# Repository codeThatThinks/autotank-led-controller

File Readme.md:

# autotank-led-hw

A CANbus-enabled LED and GPIO controller -- PCB design files

## Theory of Operation

The controller listens for messages on the CANbus and drives two addressable RGB LED strips and four general-purpose open-collector outputs. It also monitors four general-purpose inputs and can send CANbus messages or change outputs in response to events.

The outputs are rated for 1A each and are intended to drive LED lights, such as headlights, tail lights, etc. The inputs are active-high and intended for body sensors and switches, such as a door switch.

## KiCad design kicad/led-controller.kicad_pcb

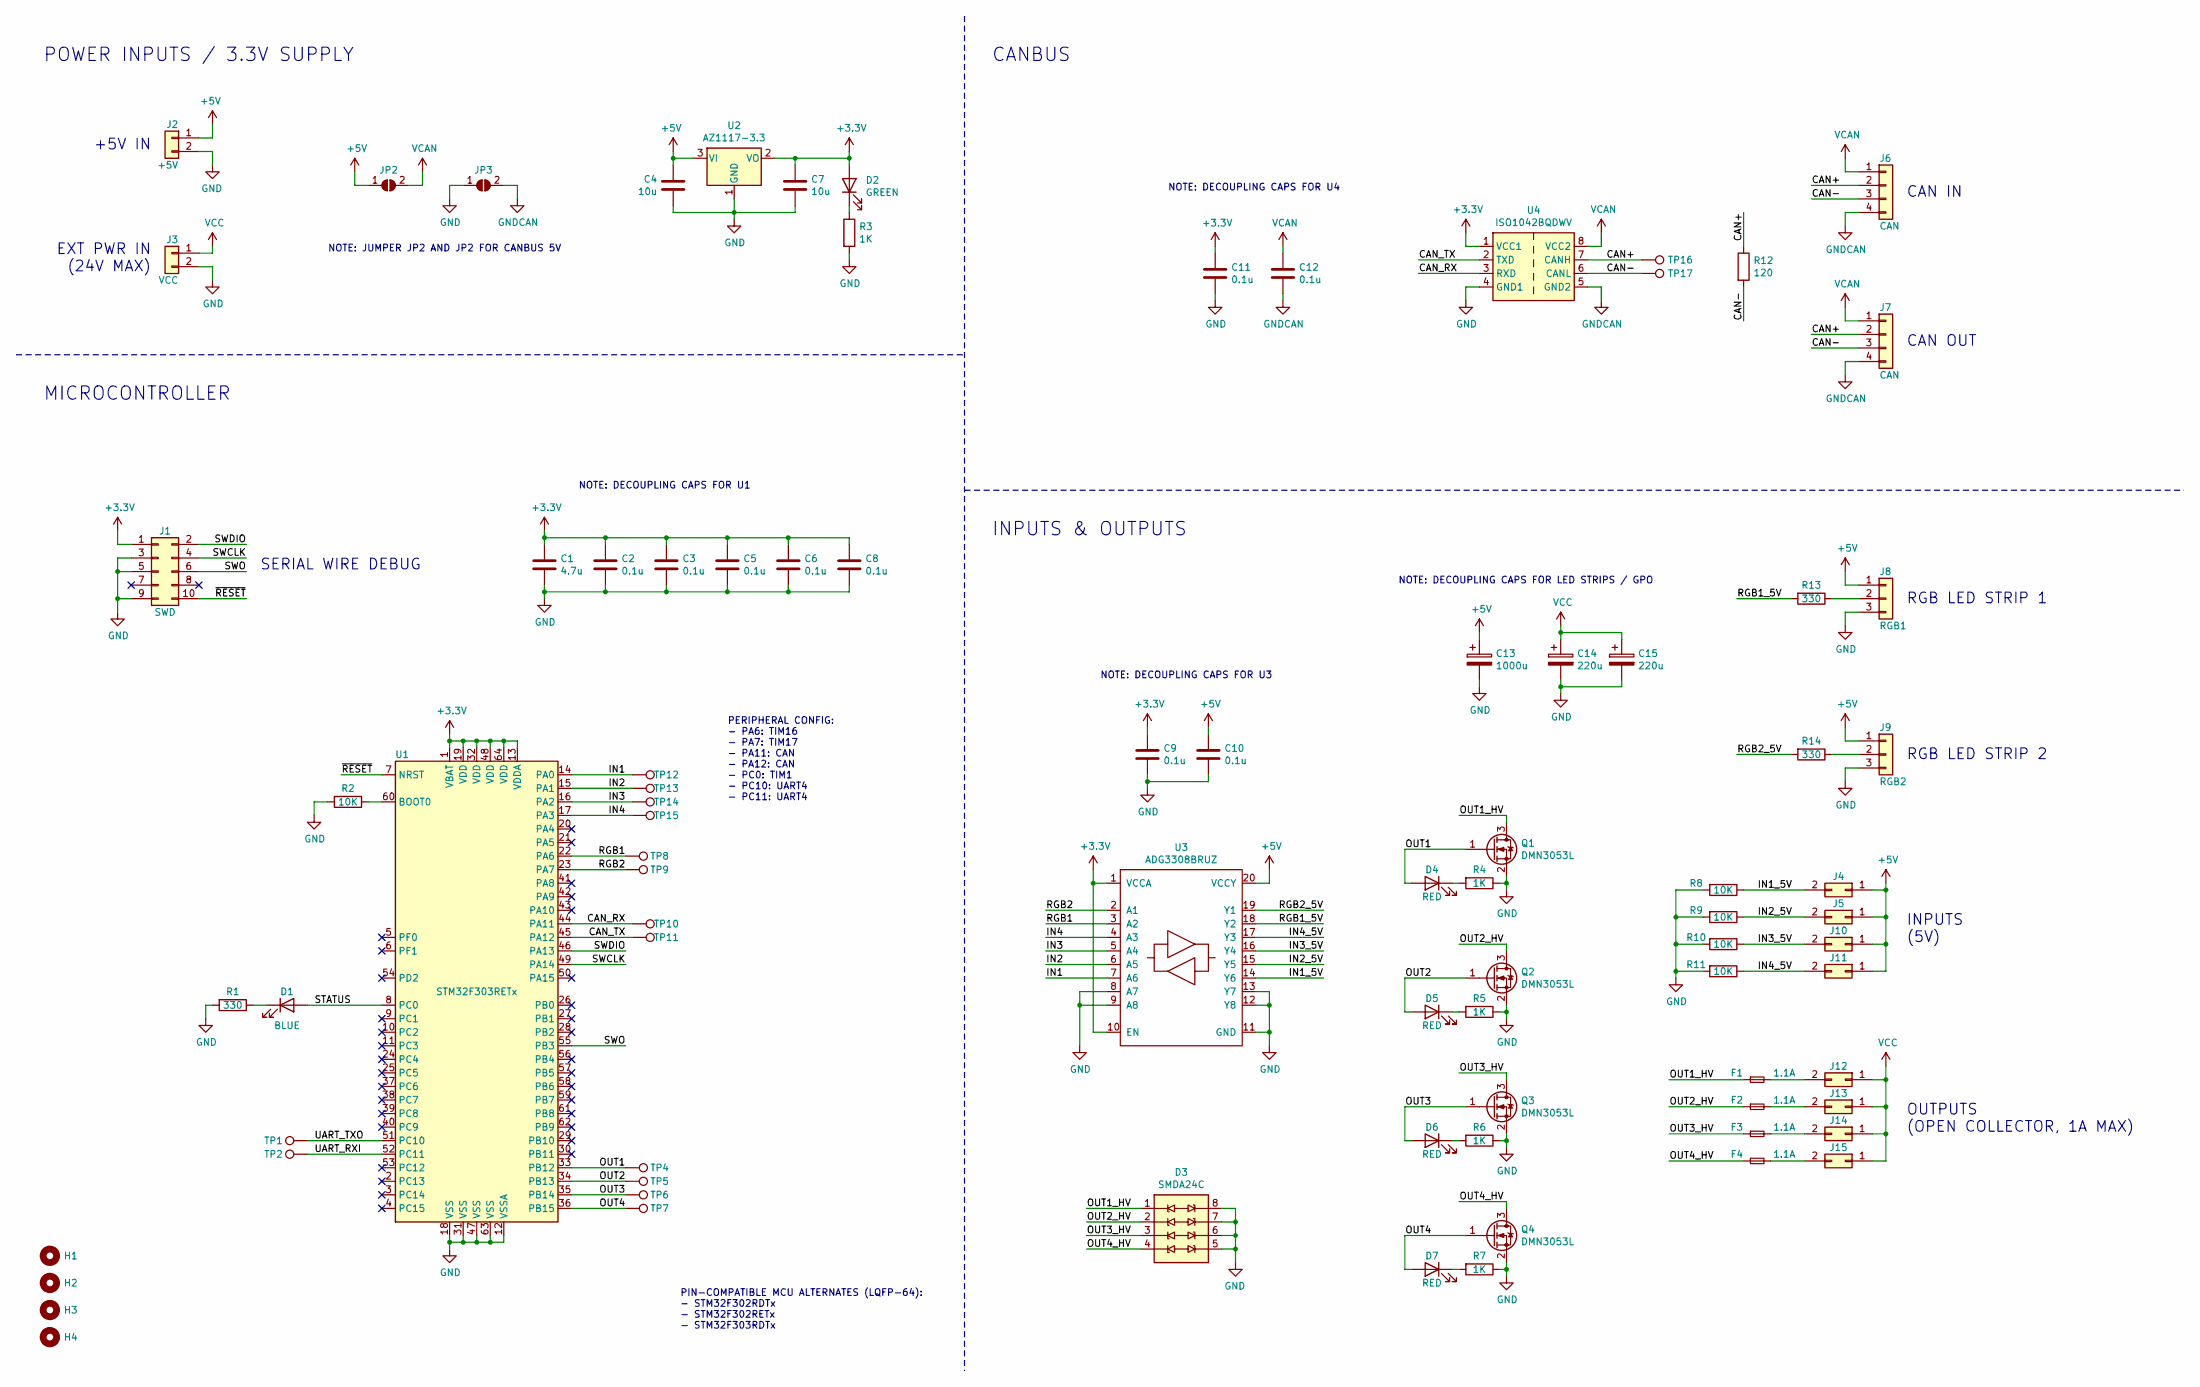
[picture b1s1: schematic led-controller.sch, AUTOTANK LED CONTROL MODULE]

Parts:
C1: 4.7u; C_0805_2012Metric
C2, C3, C5, C6, C8, C9, C10, C11, C12: 0.1u; C_0603_1608Metric
C4, C7: 10u; C_0805_2012Metric
C13: 1000u; CP_Radial_D8.0mm_P3.50mm
C14, C15: 220u; CP_Radial_D8.0mm_P3.50mm
D1: BLUE; LED_0603_1608Metric
D2: GREEN; LED_0603_1608Metric
D3: SMDA24C; SO-8_5.3x6.2mm_P1.27mm
D4, D5, D6, D7: RED; LED_0603_1608Metric
F1, F2, F3, F4: 1.1A; Fuse_1812_4532Metric_Castellated
H1, H2, H3, H4: MountingHole; MountingHole_3.2mm_M3
J1: SWD; PinHeader_2x05_P2.54mm_Vertical
J2: +5V; JST_XH_B2B-XH-AM_1x02_P2.50mm_Vertical
J3: VCC; JST_XH_B2B-XH-AM_1x02_P2.50mm_Vertical
J4: IN1; JST_XH_B2B-XH-AM_1x02_P2.50mm_Vertical
J5: IN2; JST_XH_B2B-XH-AM_1x02_P2.50mm_Vertical
J6, J7: CAN; JST_XH_B4B-XH-AM_1x04_P2.50mm_Vertical
J8: RGB1; JST_XH_B3B-XH-AM_1x03_P2.50mm_Vertical
J9: RGB2; JST_XH_B3B-XH-AM_1x03_P2.50mm_Vertical
J10: IN3; JST_XH_B2B-XH-AM_1x02_P2.50mm_Vertical
J11: IN4; JST_XH_B2B-XH-AM_1x02_P2.50mm_Vertical
J12: OUT1; JST_XH_B2B-XH-AM_1x02_P2.50mm_Vertical
J13: OUT2; JST_XH_B2B-XH-AM_1x02_P2.50mm_Vertical
J14: OUT3; JST_XH_B2B-XH-AM_1x02_P2.50mm_Vertical
J15: OUT4; JST_XH_B2B-XH-AM_1x02_P2.50mm_Vertical
JP2, JP3: SolderJumper_2_Open; SolderJumper-2_P1.3mm_Open_RoundedPad1.0x1.5mm
Q1, Q2, Q3, Q4: DMN3053L; SOT-23
R1, R13, R14: 330; R_0603_1608Metric
R2, R8, R9, R10, R11: 10K; R_0603_1608Metric
R3, R4, R5, R6, R7: 1K; R_0603_1608Metric
R12: 120; R_0603_1608Metric
TP1: TXO; TestPoint_THTPad_D1.0mm_Drill0.5mm
TP2: RXI; TestPoint_THTPad_D1.0mm_Drill0.5mm
TP4: OUT1; TestPoint_THTPad_D1.0mm_Drill0.5mm
TP5: OUT2; TestPoint_THTPad_D1.0mm_Drill0.5mm
TP6: OUT3; TestPoint_THTPad_D1.0mm_Drill0.5mm
TP7: OUT4; TestPoint_THTPad_D1.0mm_Drill0.5mm
TP8: RGB1; TestPoint_THTPad_D1.0mm_Drill0.5mm
TP9: RGB2; TestPoint_THTPad_D1.0mm_Drill0.5mm
TP10: RX; TestPoint_THTPad_D1.0mm_Drill0.5mm
TP11: TX; TestPoint_THTPad_D1.0mm_Drill0.5mm
TP12: IN1; TestPoint_THTPad_D1.0mm_Drill0.5mm
TP13: IN2; TestPoint_THTPad_D1.0mm_Drill0.5mm
TP14: IN3; TestPoint_THTPad_D1.0mm_Drill0.5mm
TP15: IN4; TestPoint_THTPad_D1.0mm_Drill0.5mm
TP16: H; TestPoint_THTPad_D1.0mm_Drill0.5mm
TP17: L; TestPoint_THTPad_D1.0mm_Drill0.5mm
U1: STM32F303RETx; LQFP-64_10x10mm_P0.5mm
U2: AZ1117-3.3; SOT-223-3_TabPin2
U3: ADG3308BRUZ; TSSOP-20_4.4x6.5mm_P0.65mm
U4: ISO1042BQDWV; SOIC-8_7.5x5.85mm_P1.27mm

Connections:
+3V3: C1.1, C2.1, C3.1, C5.1, C6.1, C7.1, C8.1, C9.1, C11.1, D2.2 (A), J1.1, U1.1 (VBAT), U1.13 (VDDA), U1.19 (VDD), U1.32 (VDD), U1.48 (VDD), U1.64 (VDD), U2.2 (VO), U3.1 (VCCA), U3.10 (EN), U4.1 (VCC1)
+5V: C4.2, C10.1, C13.1, J2.1, J4.1, J5.1, J8.1, J9.1, J10.1, J11.1, JP2.1 (A), U2.3 (VI), U3.20 (VCCY)
/CAN+: J6.2, J7.2, R12.1, TP16.1, U4.7 (CANH)
/CAN-: J6.3, J7.3, R12.2, TP17.1, U4.6 (CANL)
/CAN_RX: TP10.1, U1.44 (PA11), U4.3 (RXD)
/CAN_TX: TP11.1, U1.45 (PA12), U4.2 (TXD)
/IN1: TP12.1, U1.14 (PA0), U3.7 (A6)
/IN1_5V: J4.2, R8.1, U3.14 (Y6)
/IN2: TP13.1, U1.15 (PA1), U3.6 (A5)
/IN2_5V: J5.2, R9.1, U3.15 (Y5)
/IN3: TP14.1, U1.16 (PA2), U3.5 (A4)
/IN3_5V: J10.2, R10.1, U3.16 (Y4)
/IN4: TP15.1, U1.17 (PA3), U3.4 (A3)
/IN4_5V: J11.2, R11.1, U3.17 (Y3)
/OUT1: D4.2 (A), Q1.1 (G), TP4.1, U1.33 (PB12)
/OUT1_HV: D3.1 (TVS1A), F1.1, Q1.3 (D)
/OUT2: D5.2 (A), Q2.1 (G), TP5.1, U1.34 (PB13)
/OUT2_HV: D3.2 (TVS2A), F2.1, Q2.3 (D)
/OUT3: D6.2 (A), Q3.1 (G), TP6.1, U1.35 (PB14)
/OUT3_HV: D3.3 (TVS3A), F3.1, Q3.3 (D)
/OUT4: D7.2 (A), Q4.1 (G), TP7.1, U1.36 (PB15)
/OUT4_HV: D3.4 (TVS4A), F4.1, Q4.3 (D)
/RGB1: TP8.1, U1.22 (PA6), U3.3 (A2)
/RGB1_5V: R13.2, U3.18 (Y2)
/RGB2: TP9.1, U1.23 (PA7), U3.2 (A1)
/RGB2_5V: R14.2, U3.19 (Y1)
/STATUS: D1.2 (A), U1.8 (PC0)
/SWCLK: J1.4, U1.49 (PA14)
/SWDIO: J1.2, U1.46 (PA13)
/SWO: J1.6, U1.55 (PB3)
/UART_RXI: TP2.1, U1.52 (PC11)
/UART_TXO: TP1.1, U1.51 (PC10)
/~RESET: J1.10, U1.7 (NRST)
GND: C1.2, C2.2, C3.2, C4.1, C5.2, C6.2, C7.2, C8.2, C9.2, C10.2, C11.2, C13.2, C14.2, C15.2, D3.5 (TVS4B), D3.6 (TVS3B), D3.7 (TVS2B), D3.8 (TVS1A), J1.3, J1.5, J1.9, J2.2, J3.2, J8.3, J9.3, JP3.1 (A), Q1.2 (S), Q2.2 (S), Q3.2 (S), Q4.2 (S), R1.2, R2.2, R3.2, R4.1, R5.1, R6.1, R7.1, R8.2, R9.2, R10.2, R11.2, U1.12 (VSSA), U1.18 (VSS), U1.31 (VSS), U1.47 (VSS), U1.63 (VSS), U2.1 (GND), U3.8 (A7), U3.9 (A8), U3.11 (GND), U3.12 (Y8), U3.13 (Y7), U4.4 (GND1)
GNDCAN: C12.2, J6.4, J7.4, JP3.2 (B), U4.5 (GND2)
unnamed: D1.1 (K), R1.1
unnamed: D2.1 (K), R3.1
unnamed: D4.1 (K), R4.2
unnamed: D5.1 (K), R5.2
unnamed: D6.1 (K), R6.2
unnamed: D7.1 (K), R7.2
unnamed: F1.2, J12.2
unnamed: F2.2, J13.2
unnamed: F3.2, J14.2
unnamed: F4.2, J15.2
unnamed: J8.2, R13.1
unnamed: J9.2, R14.1
unnamed: R2.1, U1.60 (BOOT0)
VCAN: C12.1, J6.1, J7.1, JP2.2 (B), U4.8 (VCC2)
VCC: C14.1, C15.1, J3.1, J12.1, J13.1, J14.1, J15.1

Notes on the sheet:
SERIAL WIRE DEBUG
CAN IN
CAN OUT
POWER INPUTS / 3.3V SUPPLY
MICROCONTROLLER
CANBUS
INPUTS & OUTPUTS
NOTE: DECOUPLING CAPS FOR U4
+5V IN
RGB LED STRIP 1
RGB LED STRIP 2
NOTE: DECOUPLING CAPS FOR U3
NOTE: DECOUPLING CAPS FOR U1
PIN-COMPATIBLE MCU ALTERNATES (LQFP-64): - STM32F302RDTx - STM32F302RETx - STM32F303RDTx
PERIPHERAL CONFIG: - PA6: TIM16 - PA7: TIM17 - PA11: CAN - PA12: CAN - PC0: TIM1 - PC10: UART4 - PC11: UART4
INPUTS (5V)
OUTPUTS (OPEN COLLECTOR, 1A MAX)
NOTE: DECOUPLING CAPS FOR LED STRIPS / GPO
NOTE: JUMPER JP2 AND JP2 FOR CANBUS 5V
EXT PWR IN (24V MAX)

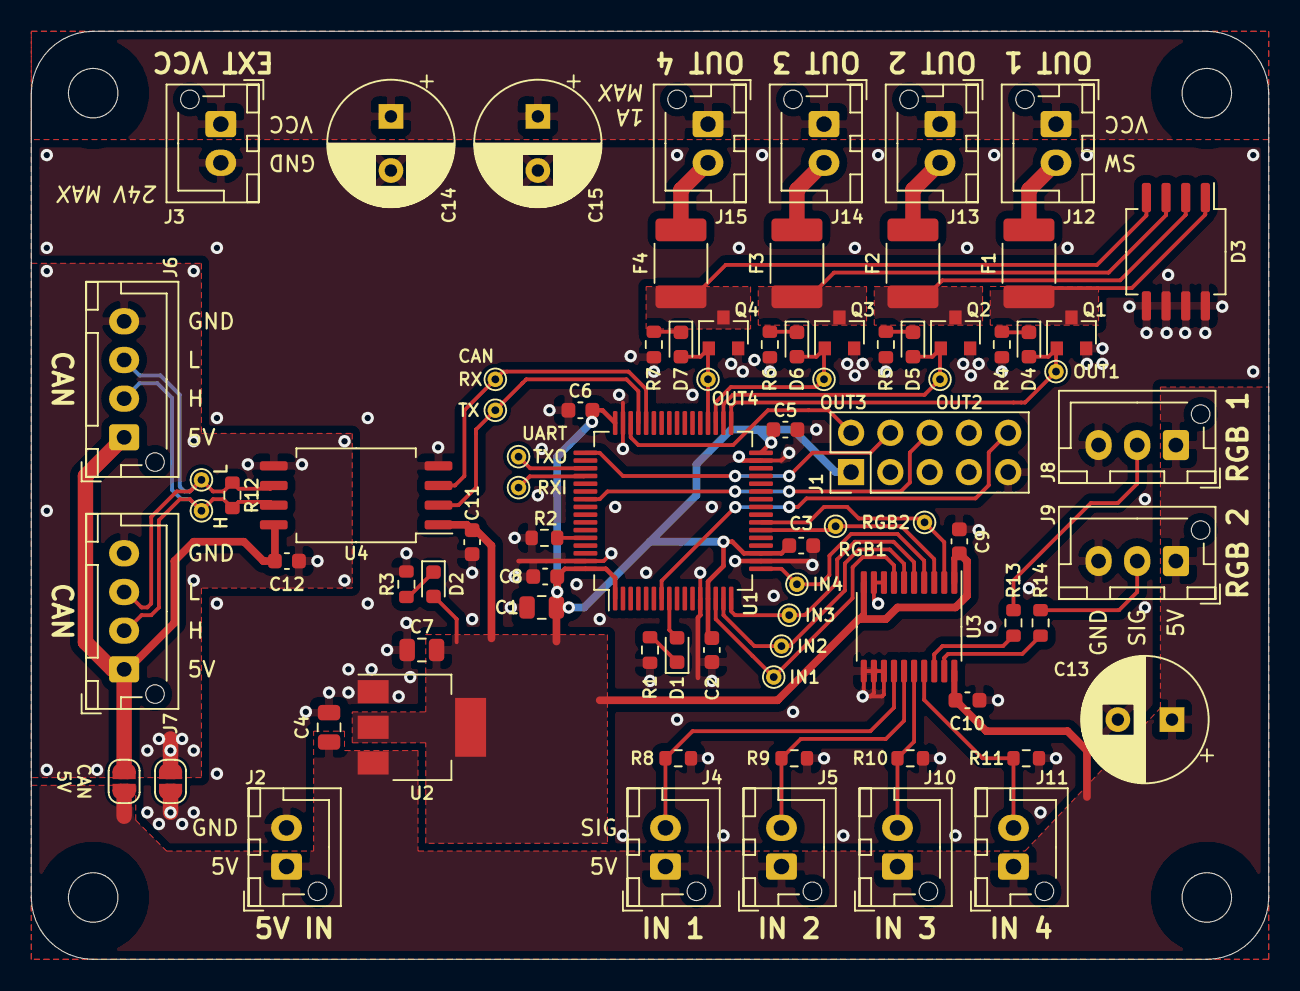
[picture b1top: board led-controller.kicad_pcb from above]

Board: 2 copper layers, 80.0 x 60.0 mm, 85 parts (0 on the bottom side), 50 nets.

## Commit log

2021-06-25 Add interactive BOM; move assembly files to own folder
2021-06-25 Add photo of assembled PCB
